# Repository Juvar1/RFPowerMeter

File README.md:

# RFPowerMeter
RF power meter and supply voltage meter for battery powered transmitter.

## First prototype

Version 1.0

## 3D image

Version 1.1

## Introduction

This meter measures the transmitting power of the radio transmitter and the voltage of the battery used as a power source. Power is displayed in watts and dBm. The device has a three-digit LCD display. The functions are controlled by a push button. The unit will automatically turn off after one minute if the button is not pressed. By pressing about 1-2 seconds device wakes from sleep mode and show measured power in watts. By pressing again device switches to dBm mode and show power in dBm. Pressing third time device show measured supply voltage. If voltage is over measuring range display shows '999'.

Comes as a bag of parts kit and is easily assembled if customer can follow the silkscreen indicators and have beginning experience with a soldering iron. Customer will need to read the resistor bands or use a multimeter to determine the resistor sizes.

Works with single 7…14 volts DC power supply connected with DC barrel plug. Internally 5.0V voltage is used through regulator 7805. ADC reference voltage is taken from supply voltage with voltage divider. Its voltage is 2.5V. One analog input is connected with supply voltage also with voltage divider. its voltage is adjusted to a max. of 2.5V at 14V so that accurate voltage measurement is made possible.

The heart of the device is AtMega328P-PU at 16MHz clock frequency. This makes it to be Arduino™ compatible system.

For measuring power, an AD8307 chip is used. It allows the RF power to be converted to a voltage between 0 and 2.5V. The permissible power is between 0 and 1kW. The permissible frequency range is between 10MHz and 1GHz. It is possible to calibrate the measuring range by ± 3dB with on-board trimmer resistor. The output is connected to the analog input of the microcontroller.

Measurement is made with following two equations:

dBm = 40(U-1)
<br>W = 10(dBm/10)/1000

The display is a three-digit LCD display. LCD display requires AC voltage. It can be simple square wave signal from DC 5V. Frequency is not critical. It can be between 30-200Hz. Phase difference lights the segment. This device uses regular CMOS series IC’s to control LCD segments. 4056 is used to control digits. Every digit needs own IC. One 4054 is used to control two decimal points and to invert common backplane signal. Frequency is made with Arduino™ PWM output. It is about 30Hz.

Current consumption is very low because of CMOS integrated circuits used and AtMega328P power saving mode which is programmatically activated. LCD display consumes very little current compared to regular LED display. Also power measurement circuit ’chip enable’ signal is controlled with AVR.

## Casing

Physical size of device is with casing 13x13cm. PCB is 10x10cm. Dimensions excludes connectors and push button. Case is bought from Digi-Key like all other parts. It’s part number is [PIP-11766-C](https://www.digikey.fi/product-detail/en/bud-industries/PIP-11766-C/377-2127-ND/4896970). DC jack outer diameter is 5.5mm and inner 2.5mm.

## Usage examples

- Amateur radio station power meter
- Power measurement

## Circuit diagram

Revision 3: Improved supply line and button noise immunity.
<br>Revision 2: Improved measuring circuit noise immunity.

## Development stage

One prototype has been ordered so far with double sided printed circuit board and with through hole components. It is designed with KiCad. Tested and working.

## Advantages

Ease of use. The device has only one button with three functions. ’Plug-and-play’. Safe operating voltage. Safe to use. Hackable design.

## Other similar devices

Surecom SW-102 Digital Antenna Power & SWR Meter VHF/UHF 125-525MHz. Used for reference and calibration.

## Soldering

The project requires no special soldering skills. All components are their through hole versions.

## Programming

All parts are open source. The program is solely written in C++. The program is very simple and with its 200 lines of code it uses only 4.6kB of program memory. AtMega328P-PU chip is used.

The bootloader must first be programmed using external programmer. I personally like to use Arduino™ as ISP and Arduino™ IDE. Be sure to choose the Arduino™ Uno from the Tools→Board menu. After installing the bootloader, the program can be uploaded using same setup.

Program does not use any external libraries. Only standard built-in power saving related libraries are used.

## Approvals

Arduino is a registered trademark. It is still ok to build a commercial product based on Arduino. Only the name may not be the same. https://www.arduino.cc/en/Main/FAQ#toc10

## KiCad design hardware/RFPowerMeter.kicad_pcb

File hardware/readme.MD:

Printed circuit board is designed with KiCad software.

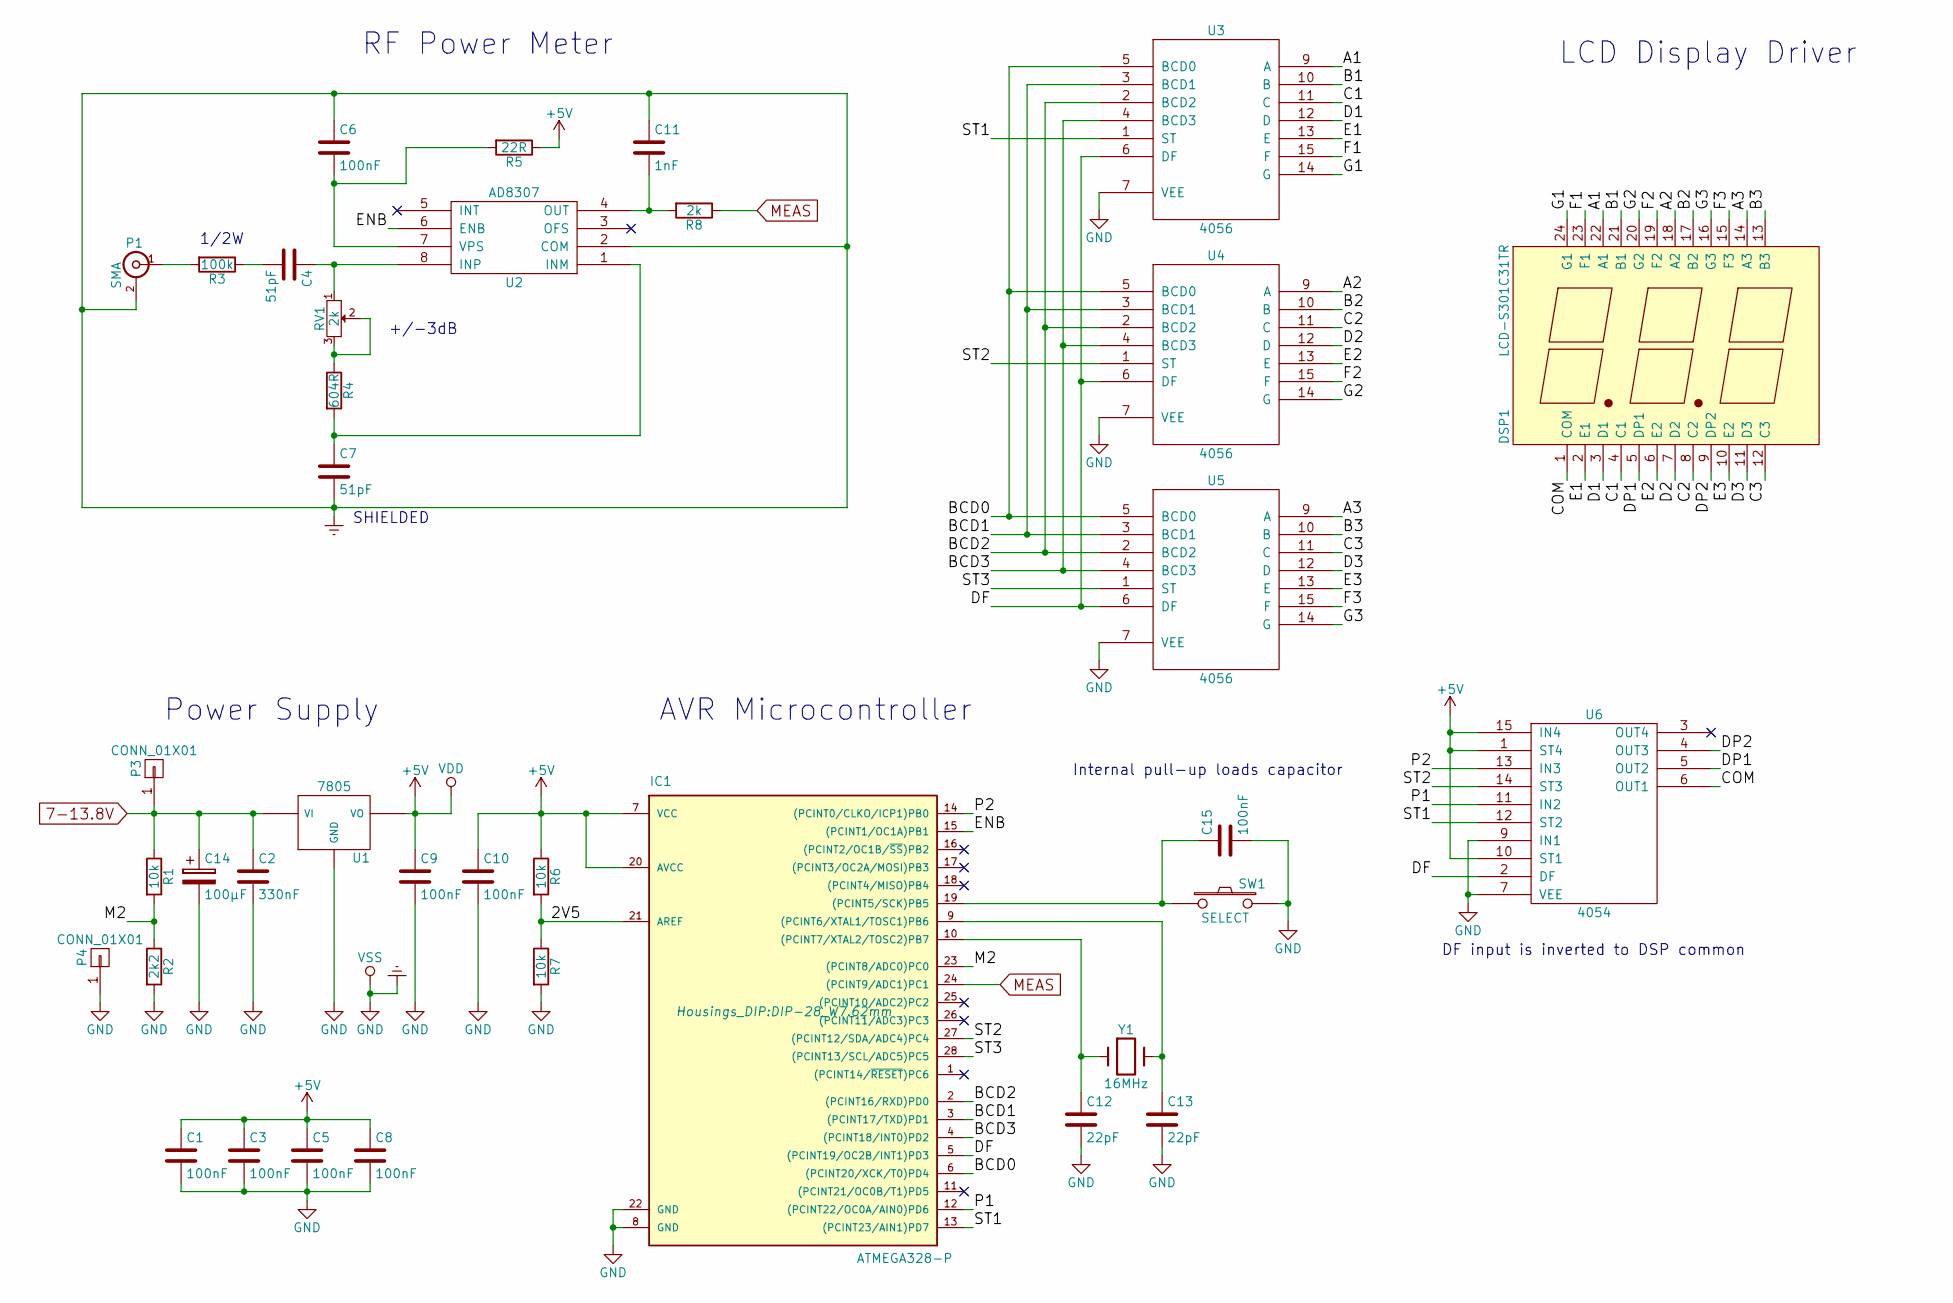
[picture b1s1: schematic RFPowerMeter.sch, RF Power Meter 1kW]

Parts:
C1, C3, C5, C6, C8, C9, C10, C15: 100nF; C_Disc_D3_P2.5
C2: 330nF; C_Disc_D3_P2.5
C4, C7: 51pF; C_Disc_D3_P2.5
C11: 1nF; C_Disc_D3_P2.5
C12, C13: 22pF; C_Disc_D3_P2.5
C14: 100µF; C_Radial_D6.3_L11.2_P2.5
DSP1: LCD-S301C31TR; LCD-24-PIN
IC1: ATMEGA328-P; DIP-28_W7.62mm
P1: SMA
P3, P4: CONN_01X01; SolderWirePad_single_1-2mmDrill
R1, R6, R7: 10k; Resistor_Horizontal_RM10mm
R2: 2k2; Resistor_Horizontal_RM10mm
R3: 100k; SolderWirePad_single_1-2mmDrill
R4: 604R; Resistor_Horizontal_RM10mm
R5: 22R; Resistor_Horizontal_RM10mm
R8: 2k; Resistor_Horizontal_RM10mm
RV1: 2k; Potentiometer_Bourns_3339P_Angular_ScrewUp
SW1: SELECT; Pin_Header_Straight_1x02
U1: 7805; TO-220_Neutral123_Horizontal
U2: AD8307; DIP-8_W7.62mm
U3, U4, U5: 4056; DIP-16_W7.62mm
U6: 4054; DIP-16_W7.62mm
Y1: 16MHz; Crystal_HC49-U_Vertical

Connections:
7-13.8V: C2.1, C14.1, P3.1, R1.1, U1.1 (VI); also elsewhere on the board
+5V: C1.1, C3.1, C5.1, C8.1, C9.1, C10.1, IC1.7 (VCC), IC1.20 (AVCC), R5.1, R6.1, U1.3 (VO), U3.16 (VDD), U4.16 (VDD), U5.16 (VDD), U6.1 (ST4), U6.10 (ST1), U6.15 (IN4), U6.16 (VDD)
/2V5: IC1.21 (AREF), R6.2, R7.1
/A1: DSP1.22 (A1), U3.9 (A)
/A2: DSP1.18 (A2), U4.9 (A)
/A3: DSP1.14 (A3), U5.9 (A)
/B1: DSP1.21 (B1), U3.10 (B)
/B2: DSP1.17 (B2), U4.10 (B)
/B3: DSP1.13 (B3), U5.10 (B)
/BCD0: IC1.6 ((PCINT20/XCK/T0)PD4), U3.5 (BCD0), U4.5 (BCD0), U5.5 (BCD0)
/BCD1: IC1.3 ((PCINT17/TXD)PD1), U3.3 (BCD1), U4.3 (BCD1), U5.3 (BCD1)
/BCD2: IC1.2 ((PCINT16/RXD)PD0), U3.2 (BCD2), U4.2 (BCD2), U5.2 (BCD2)
/BCD3: IC1.4 ((PCINT18/INT0)PD2), U3.4 (BCD3), U4.4 (BCD3), U5.4 (BCD3)
/C1: DSP1.4 (C1), U3.11 (C)
/C2: DSP1.8 (C2), U4.11 (C)
/C3: DSP1.12 (C3), U5.11 (C)
/COM: DSP1.1 (COM), U6.6 (OUT1)
/D1: DSP1.3 (D1), U3.12 (D)
/D2: DSP1.7 (D2), U4.12 (D)
/D3: DSP1.11 (D3), U5.12 (D)
/DF: IC1.5 ((PCINT19/OC2B/INT1)PD3), U3.6 (DF), U4.6 (DF), U5.6 (DF), U6.2 (DF)
/DP1: DSP1.5 (DP1), U6.5 (OUT2)
/DP2: DSP1.9 (DP2), U6.4 (OUT3)
/E1: DSP1.2 (E1), U3.13 (E)
/E2: DSP1.6 (E2), U4.13 (E)
/E3: DSP1.10 (E2), U5.13 (E)
/ENB: IC1.15 ((PCINT1/OC1A)PB1), U2.6 (ENB)
/F1: DSP1.23 (F1), U3.15 (F)
/F2: DSP1.19 (F2), U4.15 (F)
/F3: DSP1.15 (F3), U5.15 (F)
/G1: DSP1.24 (G1), U3.14 (G)
/G2: DSP1.20 (G2), U4.14 (G)
/G3: DSP1.16 (G3), U5.14 (G)
/M2: IC1.23 ((PCINT8/ADC0)PC0), R1.2, R2.1
/P1: IC1.12 ((PCINT22/OC0A/AIN0)PD6), U6.11 (IN2)
/P2: IC1.14 ((PCINT0/CLKO/ICP1)PB0), U6.13 (IN3)
/ST1: IC1.13 ((PCINT23/AIN1)PD7), U3.1 (ST), U6.12 (ST2)
/ST2: IC1.27 ((PCINT12/SDA/ADC4)PC4), U4.1 (ST), U6.14 (ST3)
/ST3: IC1.28 ((PCINT13/SCL/ADC5)PC5), U5.1 (ST)
Earth: C1.2, C2.2, C3.2, C5.2, C6.1, C7.2, C8.2, C9.2, C10.2, C11.1, C12.2, C13.2, C14.2, C15.2, IC1.8 (GND), IC1.22 (GND), P1.2 (Ext), P4.1, R2.2, R7.2, SW1.2, U1.2 (GND), U1.4 (GND), U2.2 (COM), U3.7 (VEE), U3.8 (VSS), U4.7 (VEE), U4.8 (VSS), U5.7 (VEE), U5.8 (VSS), U6.7 (VEE), U6.8 (VSS), U6.9 (IN1); also elsewhere on the board
MEAS: IC1.24 ((PCINT9/ADC1)PC1), R8.1
unnamed: C4.1, RV1.1, U2.8 (INP)
unnamed: C4.2, R3.1
unnamed: C6.2, R5.2, U2.7 (VPS)
unnamed: C7.1, R4.2, U2.1 (INM)
unnamed: C11.2, R8.2, U2.4 (OUT)
unnamed: C12.1, IC1.10 ((PCINT7/XTAL2/TOSC2)PB7), Y1.1
unnamed: C13.1, IC1.9 ((PCINT6/XTAL1/TOSC1)PB6), Y1.2
unnamed: C15.1, IC1.19 ((PCINT5/SCK)PB5), SW1.1
unnamed: P1.1 (In), R3.2
unnamed: R4.1, RV1.2, RV1.3

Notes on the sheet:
1/2W
SHIELDED
RF Power Meter
LCD Display Driver
AVR Microcontroller
Power Supply
DF input is inverted to DSP common
+/-3dB
Internal pull-up loads capacitor

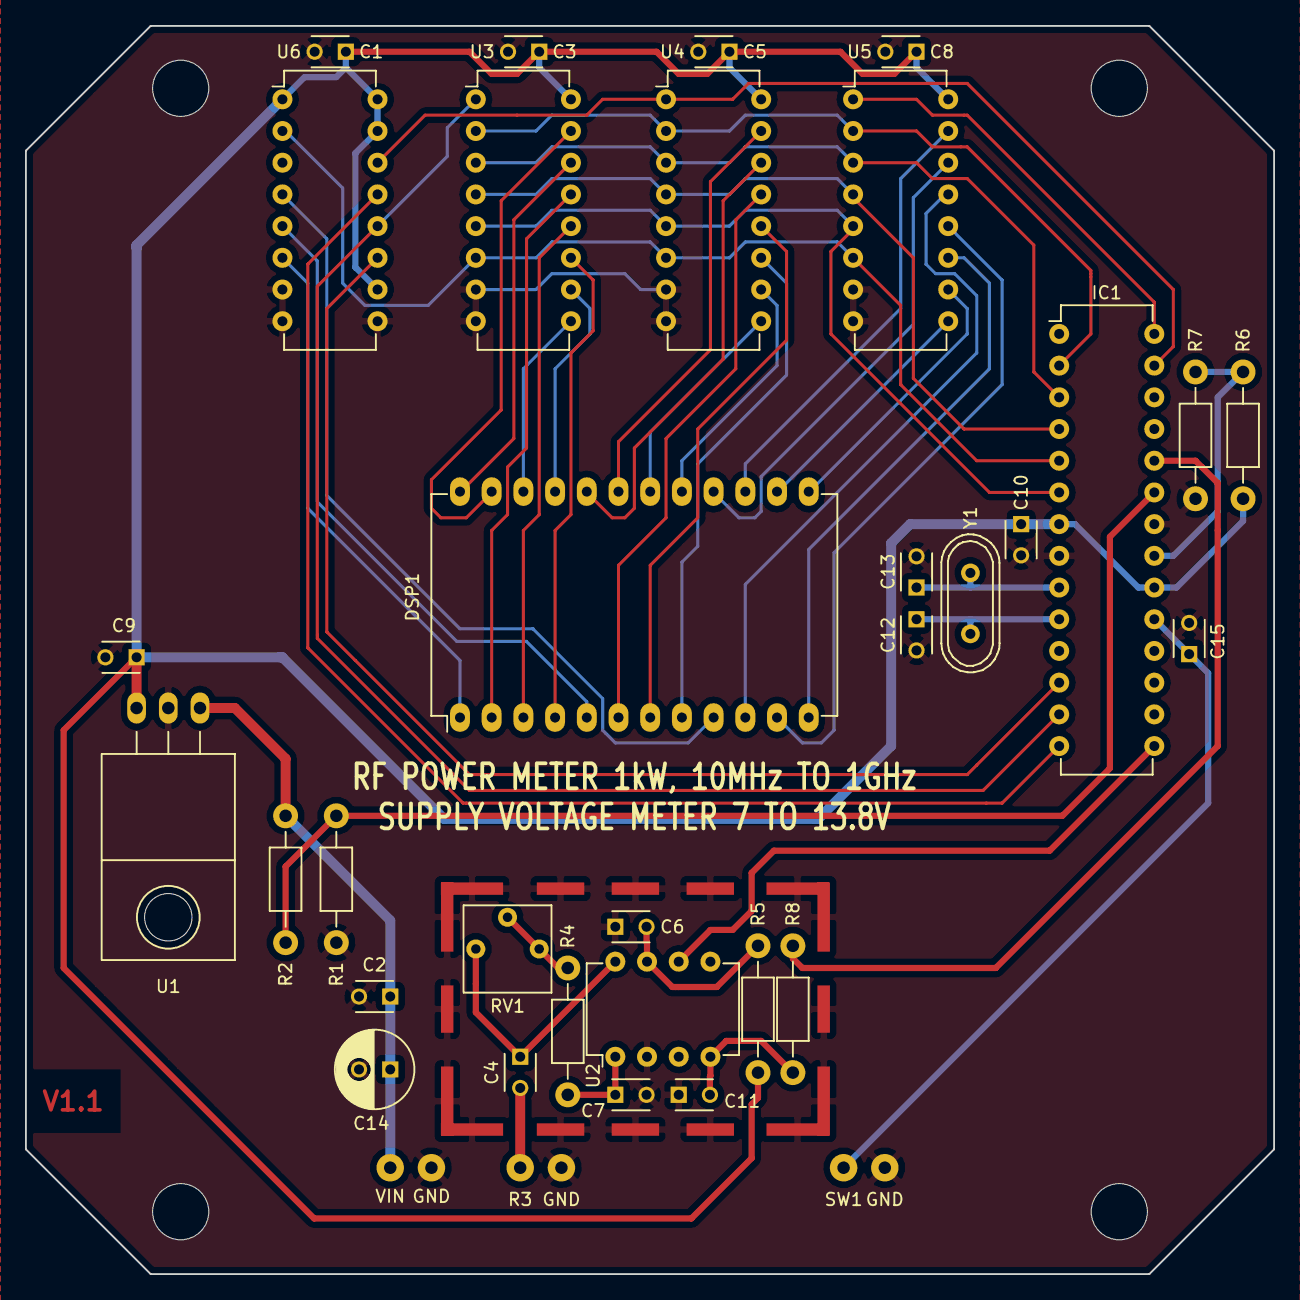
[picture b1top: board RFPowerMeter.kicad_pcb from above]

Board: 2 copper layers, 100.0 x 100.0 mm, 38 parts (0 on the bottom side), 50 nets.

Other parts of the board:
GND: SolderWirePad_single_1-2mmDrill
GND#2: CONN_01X01; SolderWirePad_single_1-2mmDrill
GND#3: SolderWirePad_single_1-2mmDrill
VIN: CONN_01X01; SolderWirePad_single_1-2mmDrill

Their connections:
7-13.8V: VIN.1; also elsewhere on the board
Earth: GND.1, GND#2.1, GND#3.1; also elsewhere on the board

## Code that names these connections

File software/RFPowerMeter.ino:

/* RFPowerMeter.ino
 * 
 * Displays 12V lead acid battery voltage level on display
 * and RF transmitting power on same display in watts or dBm
 * 
 * Author: jpvarjonen@gmail.com
 * Copyright (C) 2019 Juha-Pekka Varjonen
 * 
 * Goes to sleep and wakes every 2s to check button state
 */

#include <avr/sleep.h>
#include <avr/wdt.h>
#include <avr/power.h>

int measureState = 0;
int buttonState;             // the current reading from the input pin
int lastButtonState = HIGH;   // the previous reading from the input pin

unsigned long lastDebounceTime = 0;  // the last time the output pin was toggled
unsigned long debounceDelay = 100;   // the debounce time; increase if the output flickers
unsigned long shutdownDelay = 0;

void setup() {
  // power up settings
  wdt_enable(WDTO_2S);

  // display frequency always on
  TCCR2A = B00000000;
  TCCR2B = B00000110; //61Hz
  analogWrite(3,128); // 50% duty cycle

  // define outputs, default output state is low
  pinMode(0,OUTPUT);  // BCD2
  pinMode(1,OUTPUT);  // BCD1
  pinMode(2,OUTPUT);  // BCD3
  pinMode(4,OUTPUT);  // BCD0
  pinMode(6,OUTPUT);  // P1
  pinMode(7,OUTPUT);  // ST1
  pinMode(8,OUTPUT);  // P2
  pinMode(9,OUTPUT);  // ENB
  pinMode(A4,OUTPUT); // ST2
  pinMode(A5,OUTPUT); // ST3

  pinMode(13,INPUT_PULLUP); //button
  if (!digitalRead(13)) { // if pressed then wake up
    // set analog reference voltage to external
    analogReference(EXTERNAL); // 2.5V set by hardware
    // activate measurement
    digitalWrite(9, HIGH);
  } else {
    // if not pressed then go back to sleep
    goToSleep();
  }
}

void loop() {

  wdt_reset(); // prevent sleep

  changeReading(); // read button state, takes >500ms

  wdt_reset(); // prevent sleep

  long result = 0; // decimal point removed with '* 100'
  if (measureState == 0) { // RF power in watts
    float val = analogRead(A1);
    float PdBm = 40*((2.5/1023*val)-1);
    float PW = pow(10,(PdBm/10))/1000;
    result = (long)(PW * 100);
  }
  else if (measureState == 1) { // RF power in dBm
    float val = analogRead(A1);
    float PdBm = 40*((2.5/1023*val)-1);
    result = (long)(PdBm * 100);
  }
  else if (measureState == 2) { // supply voltage measurement
    float val = analogRead(A0);
    float voltage = (12.205/1023*val);
    if(val == 1023) voltage = 999;
    result = (long)(voltage * 100);
  }
  
  short shift = 0;

  if (result < 0) {
    shift = 1;
    result = -result;
    writeToDisplay(1, 0xe, false); // minus sign
  }
  
  boolean dp1 = false;
  boolean dp2 = false;

  if (result < 999) {
    dp1 = true;
  }
  if (result > 999) {
    result = result / 10;
    dp2 = true;
  }
  if (result > 999) {
    result = result / 10;
    dp2 = false;
  }

  writeToDisplay(1 + shift, (int)(result / 100), dp1);
  writeToDisplay(2 + shift, (int)((result % 100) / 10), dp2);
  if (shift == 0) writeToDisplay(3, (int)(result % 10), false);

  //if 1 minute is up from last button press
  if (millis() - shutdownDelay >= 60000) {
    writeToDisplay(1,0xf,false);
    writeToDisplay(2,0xf,false);
    writeToDisplay(3,0xf,false);
    digitalWrite(9, LOW); // deactivate measurement
    goToSleep();
  }
  
}

void changeReading() {
  int reading = digitalRead(13);
  // If the switch changed, due to noise or pressing:
  if (reading != lastButtonState) {
    // reset the debouncing timer
    lastDebounceTime = millis();
  }
    if ((millis() - lastDebounceTime) > debounceDelay) {
    // whatever the reading is at, it's been there for longer than the debounce
    // delay, so take it as the actual current state:

    // if the button state has changed:
    if (reading != buttonState) {
      buttonState = reading;

      // only use state if the new button state is LOW
      if (buttonState == LOW) {
        measureState++;
        if(measureState > 2) { measureState = 0; }
        
        // display measurement state 'icon'
        if(measureState == 0) {
          writeToDisplay(1,0xc,false); //P
          writeToDisplay(2,0,false);   //0
          writeToDisplay(3,1,false);   //1
        } else if(measureState == 1) {
          writeToDisplay(1,0xc,false); //P
          writeToDisplay(2,0,false);   //0
          writeToDisplay(3,2,false);   //2
        } else if(measureState == 2) {
          writeToDisplay(1,0xb,false); //H
          writeToDisplay(2,1,false);   //1
          writeToDisplay(3,0xf,false); //(blank)
        }
        delay(500);
        shutdownDelay = millis(); // button resets the timeout
      }
    }
  }
  // save the reading. Next time through the loop, it'll be the lastButtonState:
  lastButtonState = reading;
}

void writeToDisplay(int disp, int number, boolean dp) {

  // error correction
  if(number > 0xf || number < 0) { number = 0xf; }
  if(disp > 3) { return; }

  //encode BCD code
  digitalWrite(2,(number & 0b1000) >> 3);
  digitalWrite(0,(number & 0b100) >> 2);
  digitalWrite(1,(number & 0b10) >> 1);
  digitalWrite(4,number & 0b1);
  digitalWrite(6, LOW); // decimal point initialization
  digitalWrite(8, LOW); // other decimal point

  // strobe
  if(disp == 1) {
    if(dp) { digitalWrite(6, HIGH); }
    digitalWrite(7, HIGH);
  }
  else if(disp == 2) {
    if(dp) { digitalWrite(8, HIGH); }
    digitalWrite(A4, HIGH);
  }
  else if(disp == 3) {digitalWrite(A5, HIGH);}
  delay(15);
  if(disp == 1) {digitalWrite(7, LOW);}
  else if(disp == 2) {digitalWrite(A4, LOW);}
  else if(disp == 3) {digitalWrite(A5, LOW);}
  delay(15);
}

void goToSleep() {
  // set sleep mode (not activated yet)
  set_sleep_mode(SLEEP_MODE_PWR_DOWN);
  // disable things
  power_spi_disable();
  power_usart0_disable();
  power_twi_disable();
  power_timer0_disable();
  power_timer1_disable();
  //power_timer2_disable();
  power_adc_disable();
  // go to sleep (watchdog will restart)
  sleep_mode();
}

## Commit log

2019-06-10 added image
2019-06-14 Improved noise immunity
2019-06-19 added first photo of proto
2019-06-20 tested and working version
2019-06-20 Improved noice immunity, fixed hole sizes
2019-06-20 fixed decimal point position
